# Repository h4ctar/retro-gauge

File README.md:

# Retro Gauge

## Introduction

This is an open source motorcycle tacho project with the following features:

- Analog tachometer
- Digital speedometer
- Odometer
- Trip meter
- Battery voltage
- Standard indicators (turn signals, oil pressure, neutral and high beam)
- Clock

It is housed in a classic round casing, with a retro looking 8 digit starburst LCD.

The toolchain is all open source; the PCB's are designed with KiCad and the case is designed in FreeCAD.

## System Design

The system design is simple, the only interesting decision is that the indicators all go via the microcontroller, this lets us do fun things with the indicators (test them when powered on or reuse the oil pressure indicator for other warnings).

## Microcontroller

An ATmega328P-PU microcontroller will be used to process all the inputs, and drive the outputs.

Here are all the required inputs and outputs:

| Function        | Type           | Number of pins    |
| --------------- | -------------- | ----------------- |
| Tacho           | Digital input  | 1                 |
| Speedo          | Digital input  | 1                 |
| Oil pressure    | Digital input  | 1                 |
| Turn signals    | Digital input  | 1                 |
| Neutral         | Digital input  | 1                 |
| High beam       | Digital input  | 1                 |
| Mode button     | Digital input  | 1                 |
| Battery voltage | Analog input   | 1                 |
| Stepper motor   | Digital output | 4 (could be 3)    |
| RBG LEDs        | Digital output | 1                 |
| LCD             | Digital output | 3                 |
| ISP             | Digital IO     | 3 (can be shared) |
| Real time clock | Digital IO     | 2                 |

For a total of 18 digital IOs and one analog input, the ATmega328P-PU has more than enough at 23 programmable IO lines.

The ATmega328P-PU also has 1024 bytes of EEPROM which can be used to store the configuration, trip and odometer values.

An external 16 MHz crystal will be used to run the ATmega328P-PU at it's fastest clock speed.

The microcontroller will be programmed with an in-circuit serial programmer (ICSP).
A bootloader doesnt need to be burned when using ICSP.

The low byte fuses configure the clock:

| Bit | Name   | Description                                | Value |
| --- | ------ | ------------------------------------------ | ----- |
| 7   | CKDIV8 | When set, divides the clock speed by 8     | 1     |
| 6   | CKOUT  | When set, the clock pulse is output on PB0 | 1     |
| 5   | SUT1   | Sets start up delay time                   | 1     |
| 4   | SUT0   |                                            | 1     |
| 3   | CKSEL3 | Sets the clock source                      | 1     |
| 2   | CKSEL2 |                                            | 1     |
| 1   | CKSEL1 |                                            | 1     |
| 0   | CKSEL0 |                                            | 1     |

The high byte fuses:

| Bit | Name     | Description                               | Value |
| --- | -------- | ----------------------------------------- | ----- |
| 7   | RSTDISBL | External reset disable                    | 1     |
| 6   | DWEN     | Debug wire enable                         | 1     |
| 5   | SPIEN    | Enable serial programming                 | 0     |
| 4   | WDTON    | Watchdog timer always on                  | 1     |
| 3   | EESAVE   | Preserve EEPROM memory through chip erase | 0     |
| 2   | EBOOTSZ1 | Sets the bootloder size memory            | 1     |
| 1   | EBOOTSZ0 |                                           | 1     |
| 0   | BOOTRST  | Select the reset vector                   | 0     |

The extended fuses:

| Bit | Name      | Description                       | Value |
| --- | --------- | --------------------------------- | ----- |
| 7   |           | Not used                          | 1     |
| 6   |           |                                   | 1     |
| 5   |           |                                   | 1     |
| 4   |           |                                   | 1     |
| 3   |           |                                   | 1     |
| 2   | BODLEVEL2 | Sets the brown-out detector level | 1     |
| 1   | BODLEVEL1 |                                   | 0     |
| 0   | BODLEVEL0 |                                   | 1     |

There is a simple Makefile that compiles and links the code and has targets to burn the fuses and the code.

## Power Supply

A linear voltage regulator will be used to convert the bikes rough 14V down to a smooth 5V for the rest of the system.
A smoothing capacitor is added on the bikes side to help smooth out the input before it gets to the regulator.

## Indicator Lights

There are indicator lights for low oil pressure, neutral, high beam and turn signals.

The oil pressure and neutral sensors are simple switches to ground.
So these will be directly connected to digital input pins.
I'm not sure if the internal pull ups will be good enough so there will be provision on the PCB for external pull up resistors.
There will be a diode to protect against connecting this pin to 12V on the bike.

The highbeam and turn signals indicators should light up when they see 12V.
We'll use an optocoupler to give some extra protection.
The left and right turn signals need to go through diodes to stop them turning each other on.

```
Diode forward voltage: 0.715V
Photodiode forward voltage: 1.3V
Photodiode forward current: 10mA
R1 = (14V - 0.715V - 1.3V) / 10mA = 1200 ohm ~= 1k ohm
```

```
CTR: 50%
Output current: 50% of 10mA = 5mA
Output voltage: 4V
R2 = (5V - 4V) / 5mA = 200 ohm
```

## Tachometer

There are a few choices for the tachometer pickup, an inductive or capacitive pickup on one of the spark plug wires, or a hall effect sensor on a rotating part of the engine.
The most robust solution is to go with the hall effect sensor, and the most universal location for it is in replacement of the mechanical drive off the camshaft of the original tachometer.

## Speedometer

The speedometer will also be a hall effect pickup, but will be a simpler design with a few magnets on the wheel and an NPN hall effect sensor mounted on an axel spacer.

## Real Time Clock

A PCF8563T RTC module will be used to keep the time for the clock.
It will have a coin cell to keep the clock ticking when the key is off.

## LCD

The VIM-878-DP-FC-S-LV LCD display will be used.
It is a transflective LCD so works well in both bright sunlight and at night with a backlight.
It is an 8 character 14 (plus 2) segment "starburst" display.
It has a total of (14 + 2) \* 8 = 128 segments and uses 4 backplanes.

The HT1621B will be used to drive the LCD.
There are some existing Arduino libraries to interface with it.
It can drive 32 segments by 4 commons which is exactly what is required to drive the selected LCD.

The schematic of the driver to the display follows the application notes in the datasheet and is optimised for the PCB layout.
It is controlled with 3 pins that are also used by the ICSP.

This table has the LCD segments from the datasheet and what memory address they are according to the PCB layout:

| LCD Pin | COM0 | COM1 | COM2 | COM3 | Memory address |
| ------- | ---- | ---- | ---- | ---- | -------------- |
| 1       | 1D   | 1E   | 1F   | CA1  | 31             |
| 2       | 1L   | 1K   | 1J   | 1I   | 30             |
| 3       | 2D   | 2E   | 2F   | CA2  | 29             |
| 4       | 2L   | 2K   | 2J   | 2I   | 27             |
| 5       | 3D   | 3E   | 3F   | CA3  | 28             |
| 6       | 3L   | 3K   | 3J   | 3I   | 26             |
| 7       | 4D   | 4E   | 4F   | CA4  | 25             |
| 8       | 4L   | 4K   | 4J   | 4I   | 24             |
| 9       | 5D   | 5E   | 5F   | CA5  | 23             |
| 10      | 5L   | 5K   | 5J   | 5I   | 22             |
| 11      | 6D   | 6E   | 6F   | CA6  | 21             |
| 12      | 6L   | 6K   | 6J   | 6I   | 20             |
| 13      | 7D   | 7E   | 7F   | CA7  | 19             |
| 14      | 7L   | 7K   | 7J   | 7I   | 18             |
| 15      | 8D   | 8E   | 8F   | CA8  | 17             |
| 16      | 8L   | 8K   | 8J   | 8I   | 16             |
| 17      | COM0 |      |      |      |                |
| 18      |      | COM1 |      |      |                |
| 19      |      |      | COM2 |      |                |
| 20      |      |      |      | COM3 |                |
| 21      | DP8  | 8C   | 8B   | 8A   | 15             |
| 22      | 8M   | 8N   | 8G   | 8H   | 14             |
| 23      | DP7  | 7C   | 7B   | 7A   | 13             |
| 24      | 7M   | 7N   | 7G   | 7H   | 12             |
| 25      | DP6  | 6C   | 6B   | 6A   | 11             |
| 26      | 6M   | 6N   | 6G   | 6H   | 10             |
| 27      | DP5  | 5C   | 5B   | 5A   | 9              |
| 28      | 5M   | 5N   | 5G   | 5H   | 8              |
| 29      | DP4  | 4C   | 4B   | 4A   | 7              |
| 30      | 4M   | 4N   | 4G   | 4H   | 6              |
| 31      | DP3  | 3C   | 3B   | 3A   | 5              |
| 32      | 3M   | 3N   | 3G   | 3H   | 4              |
| 33      | DP2  | 2C   | 2B   | 2A   | 3              |
| 34      | 2M   | 2N   | 2G   | 2H   | 2              |
| 35      | DP1  | 1C   | 1B   | 1A   | 1              |
| 36      | 1M   | 1N   | 1G   | 1H   | 0              |

From this table we can see that each digit is powered by 4 LCD pins that map to 4 memory addresses.
For example digit 1 is LCD pins 35, 1, 2 and 36, which map to memory address' 1, 31, 30 and 0.

The font maps ASCII characters to the segments in order CA,F,E,D,I,J,K,L,A,B,C,DP,H,G,N,M.
The segments are in this order so the nibbles match the memory layout of the driver.

The address mapping maps digits to the 4 memory addresses that the font nibbles should be written to.

| Digit | Address'   |
| ----- | ---------- |
| 1     |  1,31,30, 0|
| 2     |  3,29,27, 2|
| 3     |  5,28,26, 4|
| 4     |  7,25,24, 6|
| 5     |  9,23,22, 8|
| 6     | 11,21,20,10|
| 7     | 13,19,18,12|
| 8     | 15,17,16,14|

This font table and address mapping should be enough to display text on the LCD.

## Stepper motor

The X27.168 stepper motor will be used, it is designed for gauges and can be directly driven from a microcontroller.

People on the internet say that clamping diodes are required, so they will be added.

The X25 datasheet shows the required pattern to step the motor.

## Indicators

## PCB Design

There are three PCBs: the main board, the sensor board and the face board.
The boards are stacked using standoffs and are connected together with 2.54mm stacking header pins.

The main board has the microcontroller, stepper motor, LCD, real time clock and indicators.
The sensor board has the power supply and the signal conditioning.
The face board is the dial face and has transparent icons for the indicators.

## Case Design

The case is 3D printed out of ASA.

## EEPROM

The ODO, trip and configuration will be stored in EEPROM.

EEPROM has like 100,000 writes before it wears out, so in order to be able to store the ODO and trip we will need to be able to rotate to new address'.
To do this we will have a table at the start of the EEPROM that stores the address of each value and if the EEPROM gets corrupt we will find a new place to store it and update the table.

| Address | Size | Description            |
| ------- | ---- | ---------------------- |
| 0       | 8    | ODO Address            |
| 1       | 8    | Trip Address           |
| 2       | 8    | Wheel diameter         |
| 15      | 8    | Next available address |
| 16      | 32   | ODO value              |
| 20      | 32   | Trip value             |

## Firmware

The source code is in the `firmware/src` directory.

There is a makefile with a default target to compile and link the source into a hex file; a `burn` target to burn this hex to the micro and a `fuses` target to write the fuses.
It is configured to use avrdude and a usbtiny programmer to talk to the microcontroller, but it should be possible to modify it to use other methods.
The code is compiled with clang.
There is a compile_flags.txt file that is used to configure a language server so that Vim or Visual Studio Code can give nice completion and code navigation.

On Arch linux I install the following tools and dependencies:

 * llvm
 * clang
 * avrdude
 * avr-libc
 * lib32-glibc

## Datasheets

 * [ATmega328p](https://ww1.microchip.com/downloads/en/DeviceDoc/Atmel-7810-Automotive-Microcontrollers-ATmega328P_Datasheet.pdf)
 * [HT1621B](https://www.holtek.com/documents/10179/116711/HT1621v321.pdf)
 * [WS2812B](https://www.digikey.com.au/en/datasheets/parallaxinc/parallax-inc-28085-ws2812b-rgb-led-datasheet)

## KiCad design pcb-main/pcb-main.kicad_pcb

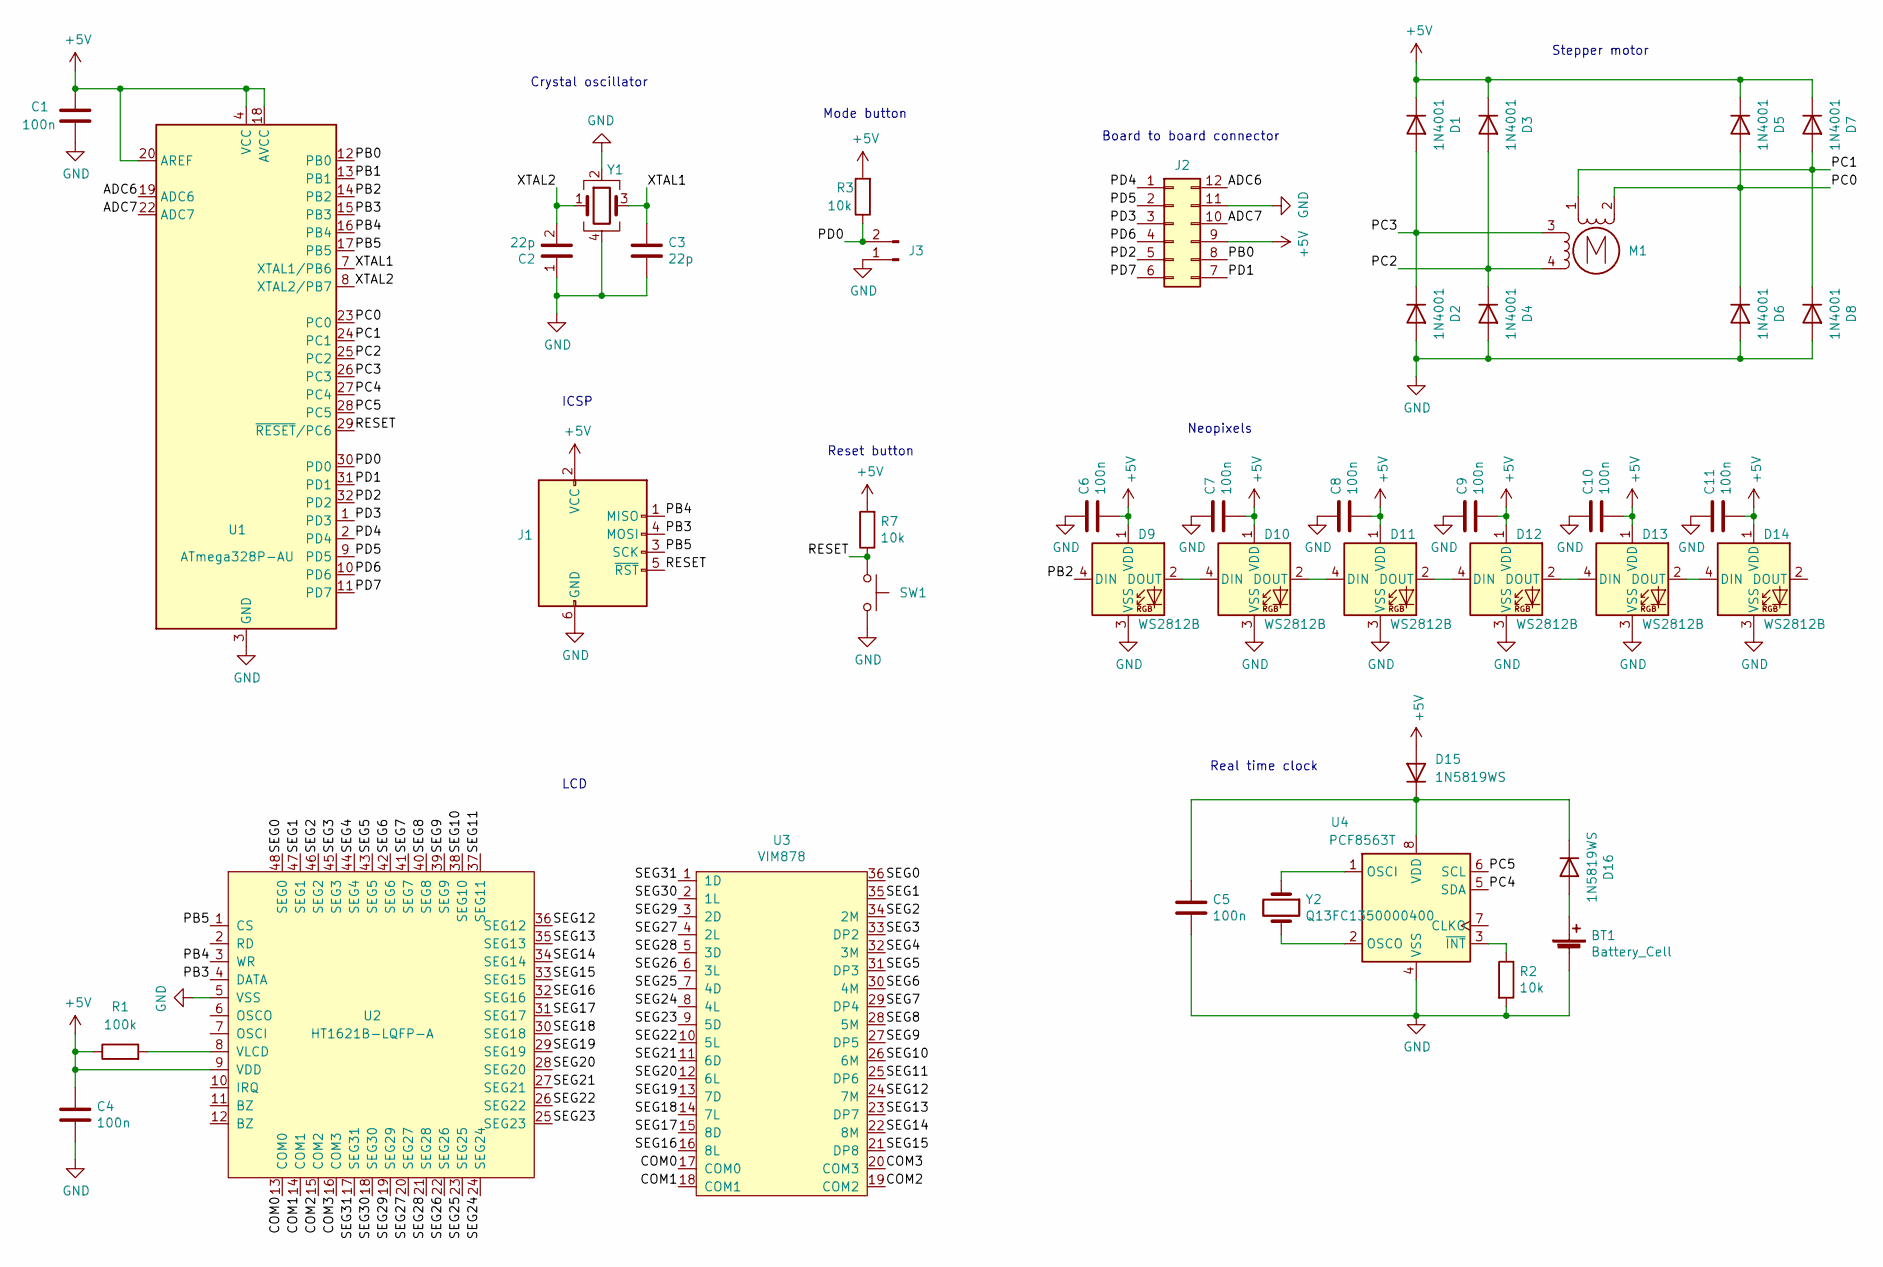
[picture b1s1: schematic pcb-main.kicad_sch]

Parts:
BT1: Battery_Cell; CR1220
C1, C4, C5, C6, C7, C8, C9, C10, C11: 100n; C_0805_2012Metric; LCSC C49678
C2, C3: 22p; C_0805_2012Metric; LCSC C1804
D1, D2, D3, D4, D5, D6, D7, D8: 1N4001; D_1206_3216Metric_Pad1.42x1.75mm_HandSolder
D9, D10, D11, D12, D13, D14: WS2812B; LED_WS2812B_PLCC4_5.0x5.0mm_P3.2mm; LCSC C2761795
D15, D16: 1N5819WS; D_SOD-323; LCSC C191023
J1: AVR-ISP-6; PinHeader_2x03_P2.54mm_Vertical
J2: Conn_02x06_Counter_Clockwise; PinHeader_2x06_P2.00mm_Vertical
J3: Conn_01x02_Male; JST_PH_S2B-PH-K_1x02_P2.00mm_Horizontal
M1: Stepper_Motor; X27.168
R1: 100k; R_0805_2012Metric; LCSC C149504
R2, R3, R7: 10k; R_0805_2012Metric; LCSC C17414
SW1: SW_Push; SW_SPST_TL3342; LCSC C318884
U1: ATmega328P-AU; TQFP-32_7x7mm_P0.8mm; LCSC C14877
U2: HT1621B-LQFP-A; LQFP-48_7x7mm_P0.5mm; LCSC C7532
U3: VIM878
U4: PCF8563T; SOIC-8_3.9x4.9mm_P1.27mm; LCSC C7440
Y1: X322516MLB4SI; Crystal_SMD_3225-4Pin_3.2x2.5mm; LCSC C13738
Y2: Q13FC1350000400; Crystal_SMD_3215-2Pin_3.2x1.5mm; LCSC C32346

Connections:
+5V: C1.1, C4.1, C6.2, C7.2, C8.2, C9.2, C10.2, C11.2, D1.1 (K), D3.1 (K), D5.1 (K), D7.1 (K), D9.1 (VDD), D10.1 (VDD), D11.1 (VDD), D12.1 (VDD), D13.1 (VDD), D14.1 (VDD), D15.2 (A), J1.2 (VCC), J2.9, R1.1, R3.2, R7.2, U1.4 (VCC), U1.6 (VCC), U1.18 (AVCC), U1.20 (AREF), U2.9 (VDD)
/ADC6: J2.12, U1.19 (ADC6)
/ADC7: J2.10, U1.22 (ADC7)
/COM0: U2.13 (COM0), U3.17 (COM0)
/COM1: U2.14 (COM1), U3.18 (COM1)
/COM2: U2.15 (COM2), U3.19 (COM2)
/COM3: U2.16 (COM3), U3.20 (COM3)
/PB0: J2.8, U1.12 (PB0)
/PB1: U1.13 (PB1)
/PB2: D9.4 (DIN), U1.14 (PB2)
/PB3: J1.4 (MOSI), U1.15 (PB3), U2.4 (DATA)
/PB4: J1.1 (MISO), U1.16 (PB4), U2.3 (WR)
/PB5: J1.3 (SCK), U1.17 (PB5), U2.1 (CS)
/PC0: D5.2 (A), D6.1 (K), M1.2 (-), U1.23 (PC0)
/PC1: D7.2 (A), D8.1 (K), M1.1, U1.24 (PC1)
/PC2: D3.2 (A), D4.1 (K), M1.4, U1.25 (PC2)
/PC3: D1.2 (A), D2.1 (K), M1.3, U1.26 (PC3)
/PC4: U1.27 (PC4), U4.5 (SDA)
/PC5: U1.28 (PC5), U4.6 (SCL)
/PD0: J3.2, R3.1, U1.30 (PD0)
/PD1: J2.7, U1.31 (PD1)
/PD2: J2.5, U1.32 (PD2)
/PD3: J2.3, U1.1 (PD3)
/PD4: J2.1, U1.2 (PD4)
/PD5: J2.2, U1.9 (PD5)
/PD6: J2.4, U1.10 (PD6)
/PD7: J2.6, U1.11 (PD7)
/RESET: J1.5 (~RST), R7.1, SW1.1, U1.29 (~RESET/PC6)
/SEG0: U2.48 (SEG0), U3.36
/SEG1: U2.47 (SEG1), U3.35
/SEG2: U2.46 (SEG2), U3.34 (2M)
/SEG3: U2.45 (SEG3), U3.33 (DP2)
/SEG4: U2.44 (SEG4), U3.32 (3M)
/SEG5: U2.43 (SEG5), U3.31 (DP3)
/SEG6: U2.42 (SEG6), U3.30 (4M)
/SEG7: U2.41 (SEG7), U3.29 (DP4)
/SEG8: U2.40 (SEG8), U3.28 (5M)
/SEG9: U2.39 (SEG9), U3.27 (DP5)
/SEG10: U2.38 (SEG10), U3.26 (6M)
/SEG11: U2.37 (SEG11), U3.25 (DP6)
/SEG12: U2.36 (SEG12), U3.24 (7M)
/SEG13: U2.35 (SEG13), U3.23 (DP7)
/SEG14: U2.34 (SEG14), U3.22 (8M)
/SEG15: U2.33 (SEG15), U3.21 (DP8)
/SEG16: U2.32 (SEG16), U3.16 (8L)
/SEG17: U2.31 (SEG17), U3.15 (8D)
/SEG18: U2.30 (SEG18), U3.14 (7L)
/SEG19: U2.29 (SEG19), U3.13 (7D)
/SEG20: U2.28 (SEG20), U3.12 (6L)
/SEG21: U2.27 (SEG21), U3.11 (6D)
/SEG22: U2.26 (SEG22), U3.10 (5L)
/SEG23: U2.25 (SEG23), U3.9 (5D)
/SEG24: U2.24 (SEG24), U3.8 (4L)
/SEG25: U2.23 (SEG25), U3.7 (4D)
/SEG26: U2.22 (SEG26), U3.6 (3L)
/SEG27: U2.20 (SEG27), U3.4 (2L)
/SEG28: U2.21 (SEG28), U3.5 (3D)
/SEG29: U2.19 (SEG29), U3.3 (2D)
/SEG30: U2.18 (SEG30), U3.2 (1L)
/SEG31: U2.17 (SEG31), U3.1 (1D)
/XTAL1: C3.1, U1.7 (XTAL1/PB6), Y1.3
/XTAL2: C2.2, U1.8 (XTAL2/PB7), Y1.1
GND: BT1.2 (-), C1.2, C2.1, C3.2, C4.2, C5.2, C6.1, C7.1, C8.1, C9.1, C10.1, C11.1, D2.2 (A), D4.2 (A), D6.2 (A), D8.2 (A), D9.3 (VSS), D10.3 (VSS), D11.3 (VSS), D12.3 (VSS), D13.3 (VSS), D14.3 (VSS), J1.6 (GND), J2.11, J3.1, R2.2, SW1.2, U1.3 (GND), U1.5 (GND), U1.21 (GND), U2.5 (VSS), U4.4 (VSS), Y1.2, Y1.4
unnamed: BT1.1 (+), D16.2 (A)
unnamed: C5.1, D15.1 (K), D16.1 (K), U4.8 (VDD)
unnamed: D10.2 (DOUT), D11.4 (DIN)
unnamed: D9.2 (DOUT), D10.4 (DIN)
unnamed: D11.2 (DOUT), D12.4 (DIN)
unnamed: D12.2 (DOUT), D13.4 (DIN)
unnamed: D13.2 (DOUT), D14.4 (DIN)
unnamed: R1.2, U2.8 (VLCD)
unnamed: R2.1, U4.3 (~INT)
unnamed: U4.1 (OSCI), Y2.1
unnamed: U4.2 (OSCO), Y2.2

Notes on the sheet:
Stepper motor
Reset button
Neopixels
ICSP
Mode button
Real time clock
Board to board connector
LCD
Crystal oscillator

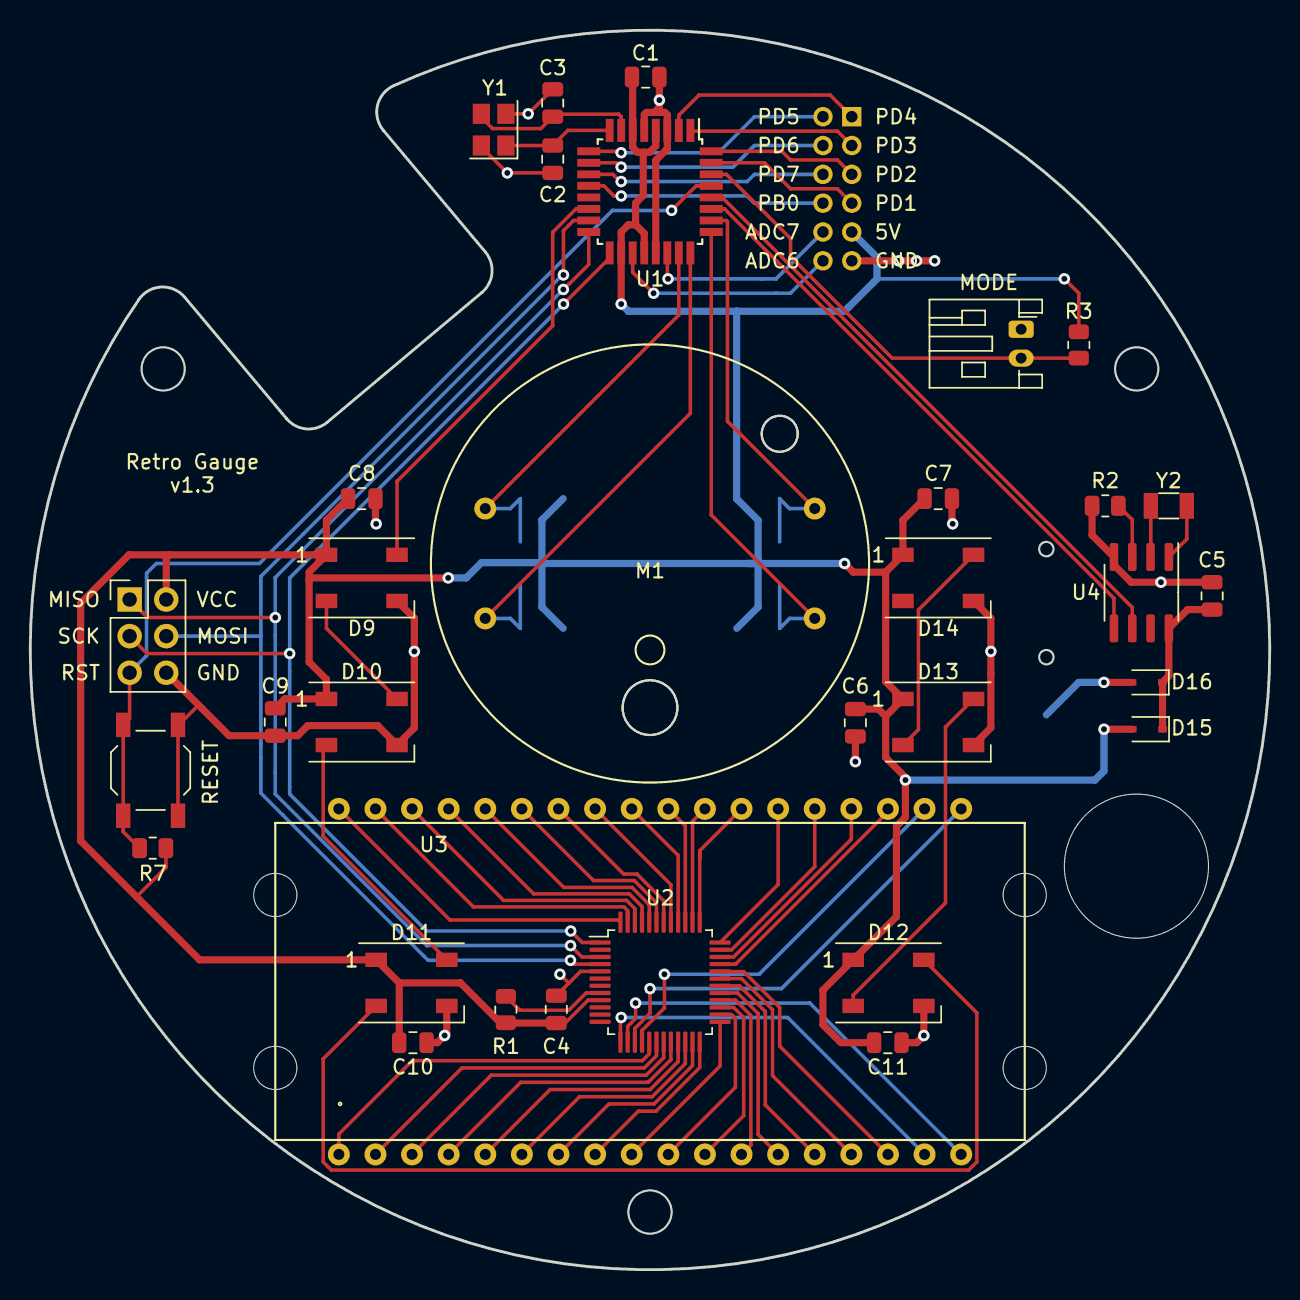
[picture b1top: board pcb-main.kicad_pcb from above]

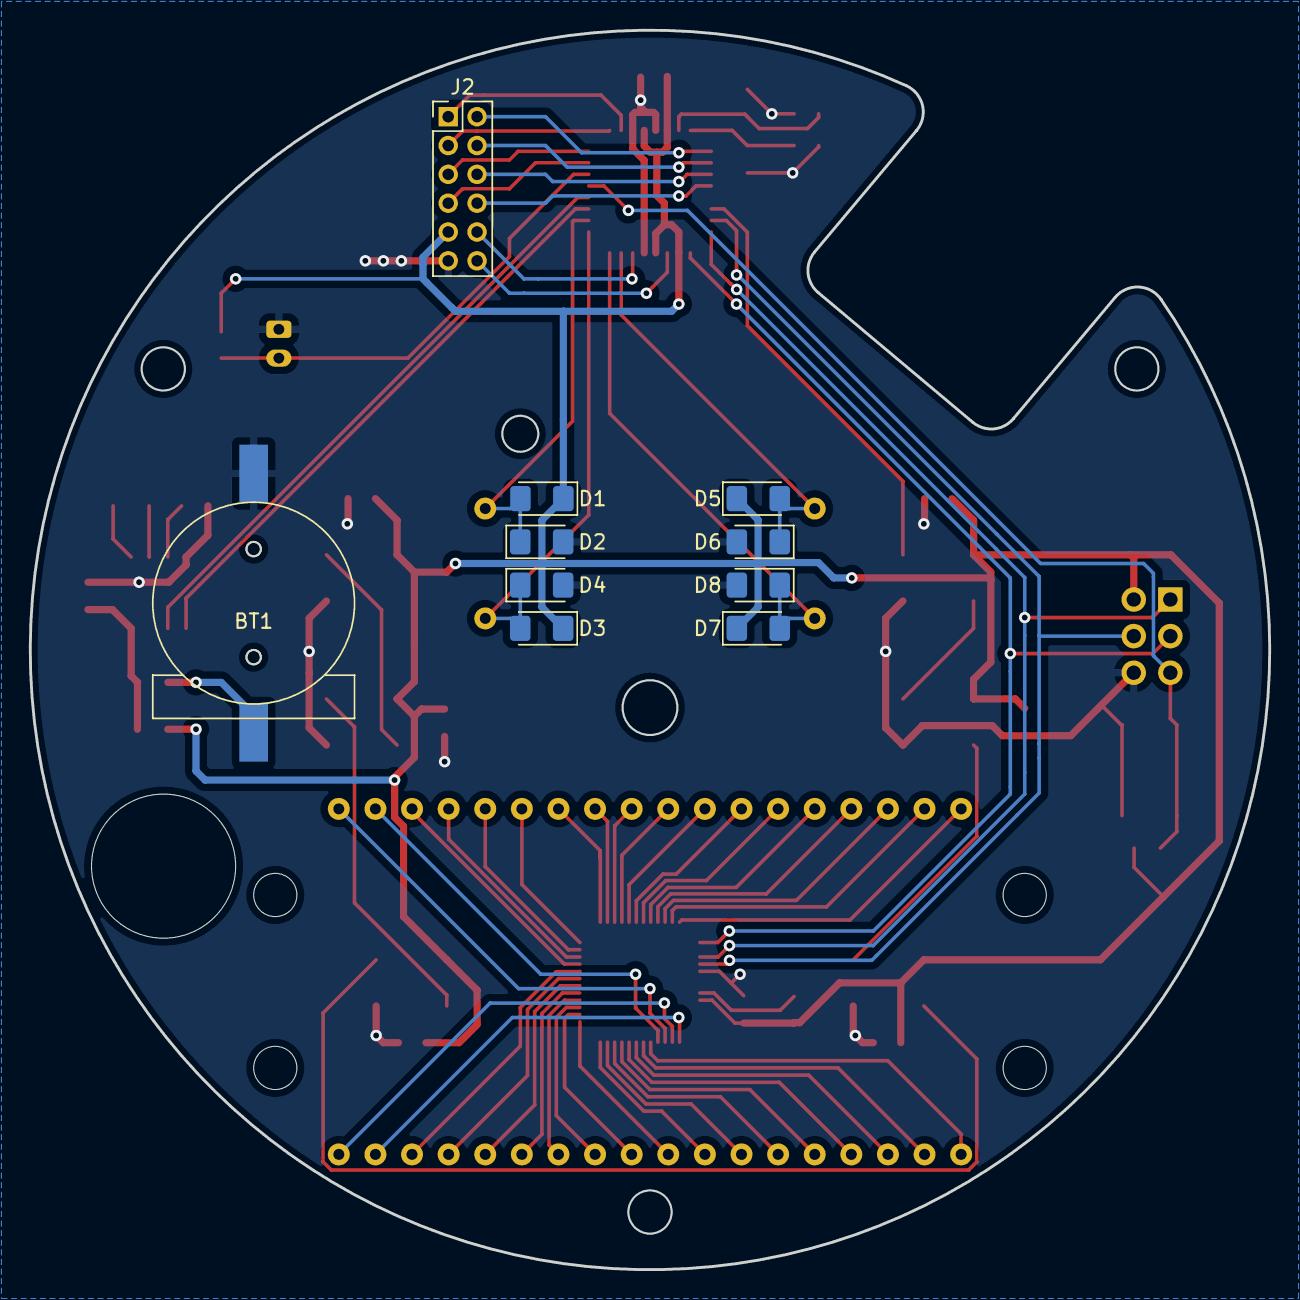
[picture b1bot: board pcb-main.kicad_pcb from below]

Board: 2 copper layers, 86.0 x 86.0 mm, 43 parts (10 on the bottom side), 73 nets.

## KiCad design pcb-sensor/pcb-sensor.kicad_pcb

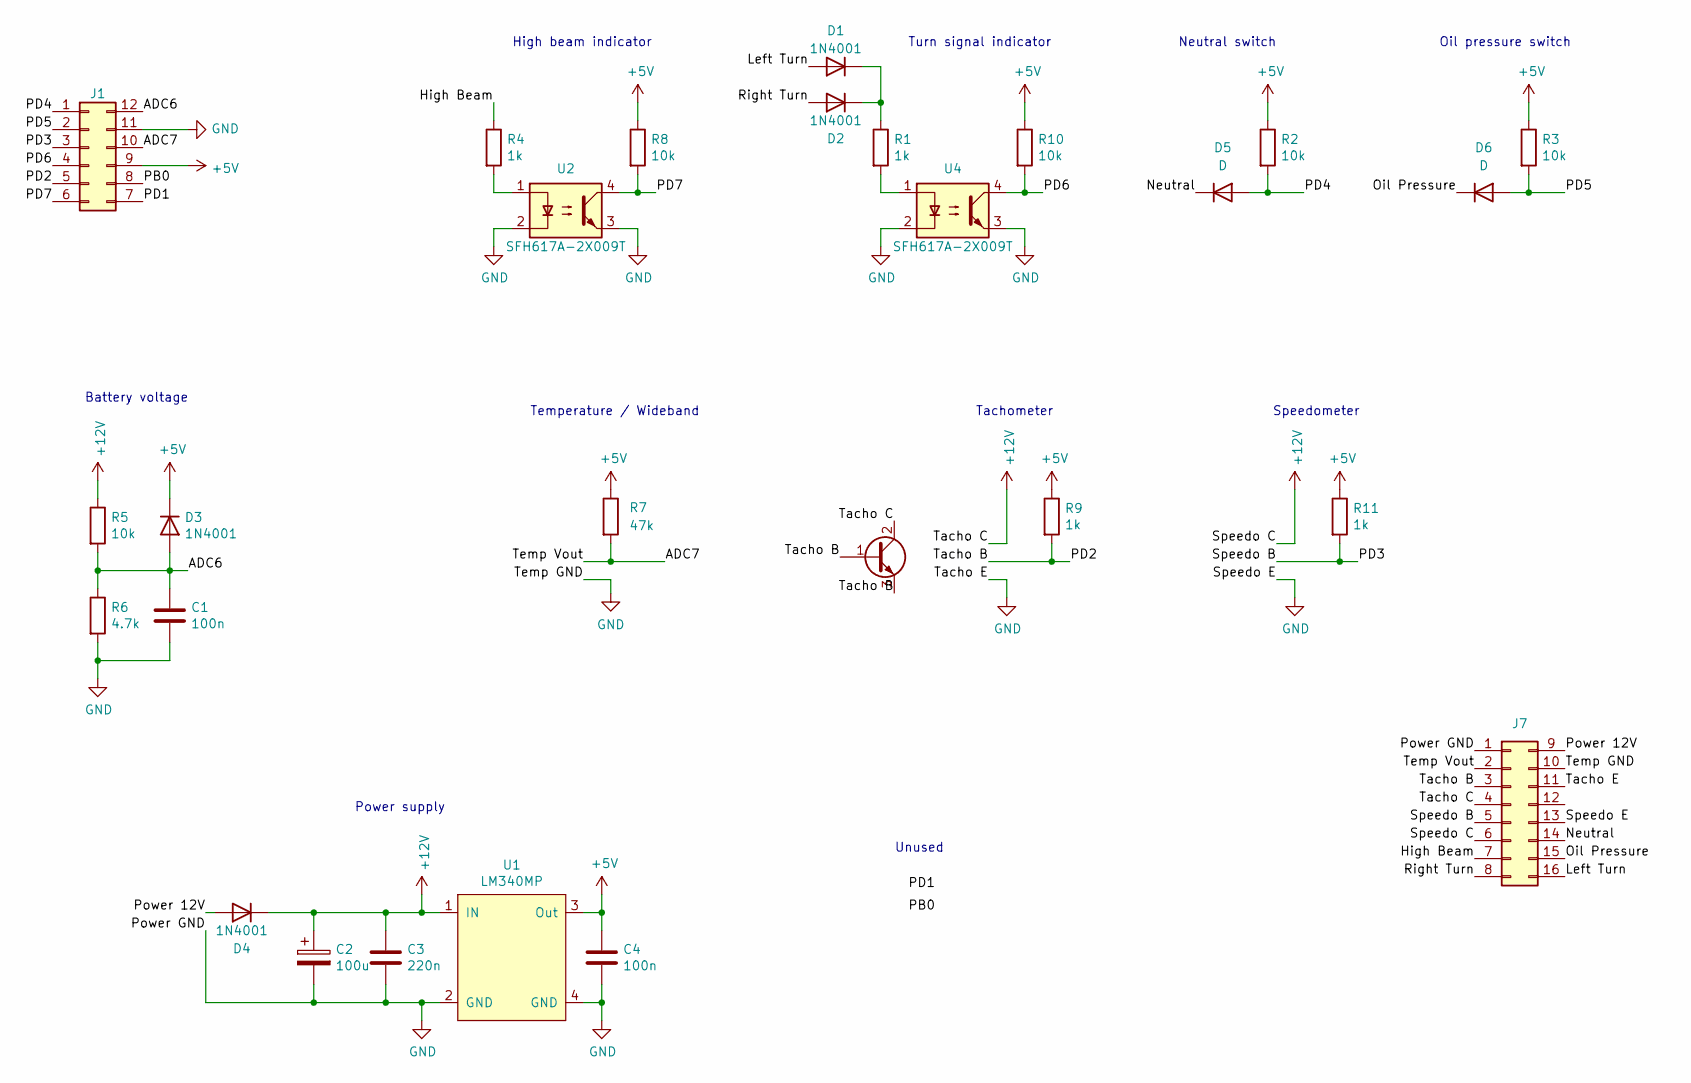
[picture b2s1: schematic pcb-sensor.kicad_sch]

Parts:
C1, C4: 100n; C_1206_3216Metric_Pad1.33x1.80mm_HandSolder
C2: 100u; CP_Radial_D8.0mm_P3.80mm
C3: 220n; C_1206_3216Metric_Pad1.33x1.80mm_HandSolder
D1, D2, D3, D4: 1N4001; D_1206_3216Metric_Pad1.42x1.75mm_HandSolder
D5, D6: D; D_1206_3216Metric_Pad1.42x1.75mm_HandSolder
J1: Conn_02x06_Counter_Clockwise; PinSocket_2x06_P2.00mm_Vertical
J7: Conn_02x08_Top_Bottom; Molex_Mini-Fit_Jr_5566-16A_2x08_P4.20mm_Vertical
R1, R4, R9, R11: 1k; R_1206_3216Metric_Pad1.30x1.75mm_HandSolder
R2, R3, R5, R8, R10: 10k; R_1206_3216Metric_Pad1.30x1.75mm_HandSolder
R6: 4.7k; R_1206_3216Metric_Pad1.30x1.75mm_HandSolder
R7: 47k; R_1206_3216Metric_Pad1.30x1.75mm_HandSolder
U1: LM340MP; SOT-223
U2, U4: SFH617A-2X009T; SMDIP-4_W7.62mm

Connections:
+5V: C4.1, D3.1 (K), J1.9, R2.1, R3.1, R7.1, R8.1, R9.1, R10.1, R11.1, U1.3 (Out)
+12V: C2.1, C3.1, D4.1 (K), J7.4, J7.6, R5.1, U1.1 (IN)
/ADC6: C1.1, D3.2 (A), J1.12, R5.2, R6.1
/High Beam: J7.7, R4.1
/Left Turn: D1.2 (A), J7.16
/Neutral: D5.1 (K), J7.14
/Oil Pressure: D6.1 (K), J7.15
/PB0: J1.8
/PD1: J1.7
/PD4: D5.2 (A), J1.1, R2.2
/PD5: D6.2 (A), J1.2, R3.2
/PD6: J1.4, R10.2, U4.4
/PD7: J1.6, R8.2, U2.4
/Power 12V: D4.2 (A), J7.9
/Right Turn: D2.2 (A), J7.8
/Speedo B: J1.3, J7.5, R11.2
/Tacho B: J1.5, J7.3, R9.2
/Temp Vout: J1.10, J7.2, R7.2
GND: C1.2, C2.2, C3.2, C4.2, J1.11, J7.1, J7.10, J7.11, J7.13, R6.2, U1.2 (GND), U1.4 (GND), U2.2, U2.3, U4.2, U4.3
unnamed: D1.1 (K), D2.1 (K), R1.1
unnamed: R1.2, U4.1
unnamed: R4.2, U2.1

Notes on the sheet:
Tachometer
Neutral switch
Unused
High beam indicator
Power supply
Battery voltage
Temperature / Wideband
Turn signal indicator
Oil pressure switch
Speedometer

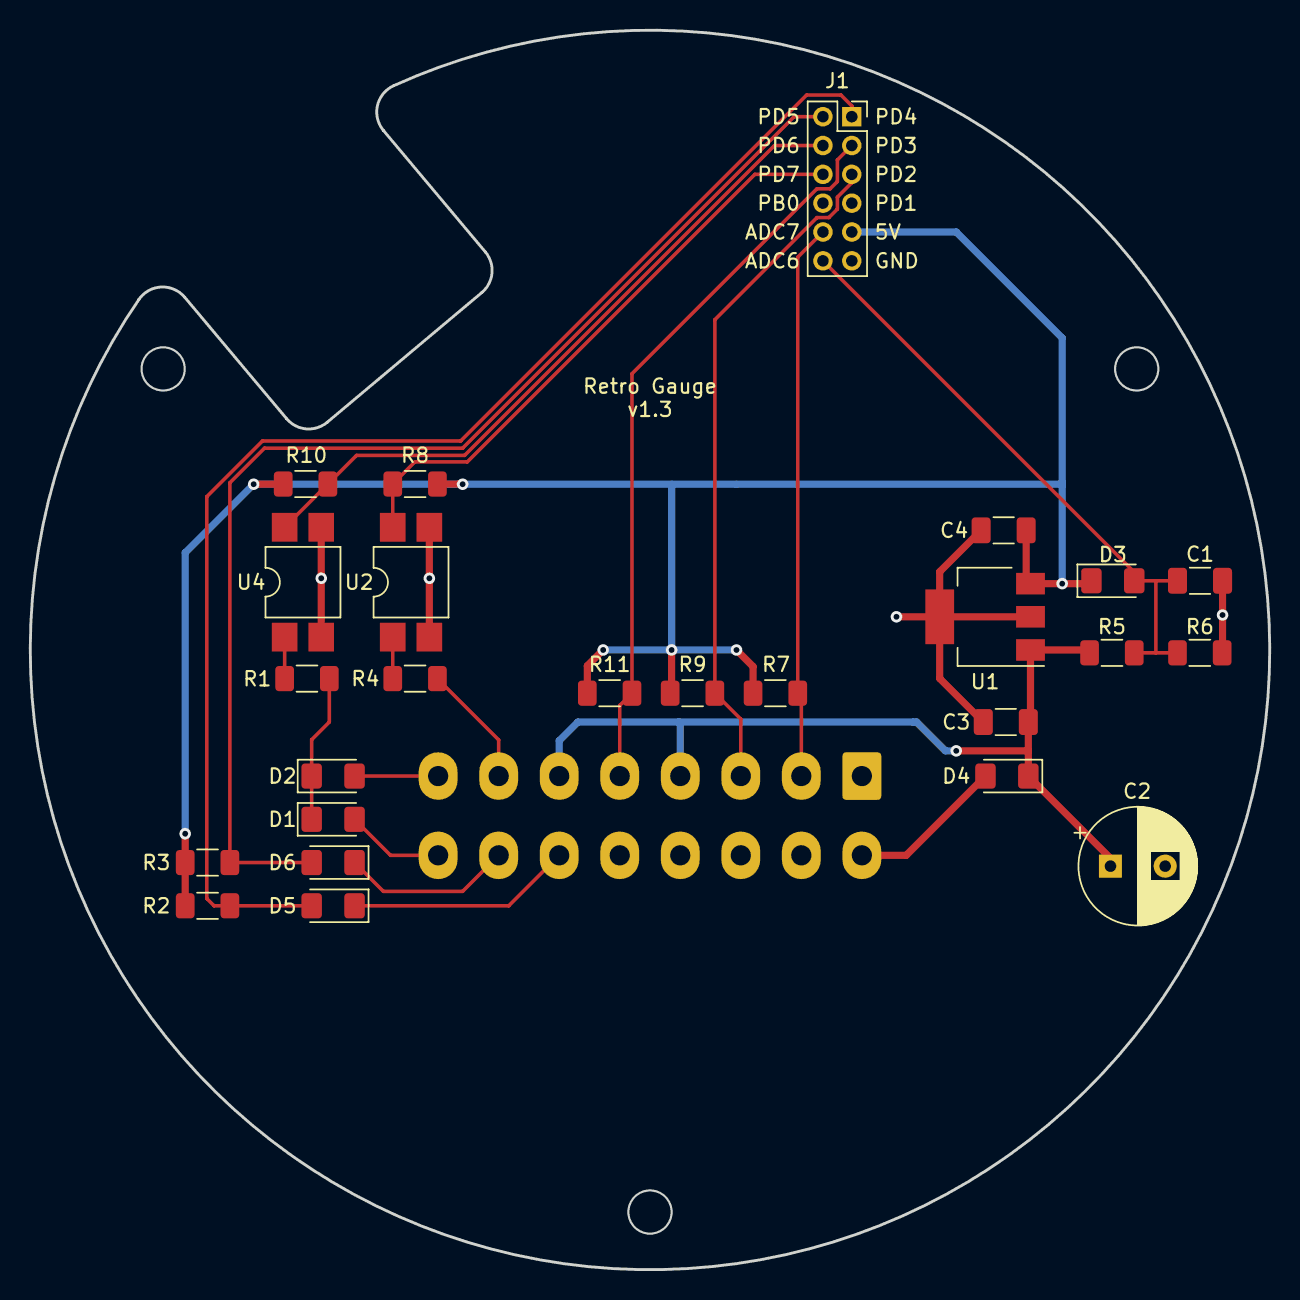
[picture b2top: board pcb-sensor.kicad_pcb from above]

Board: 2 copper layers, 86.0 x 86.0 mm, 26 parts (1 on the bottom side), 20 nets.

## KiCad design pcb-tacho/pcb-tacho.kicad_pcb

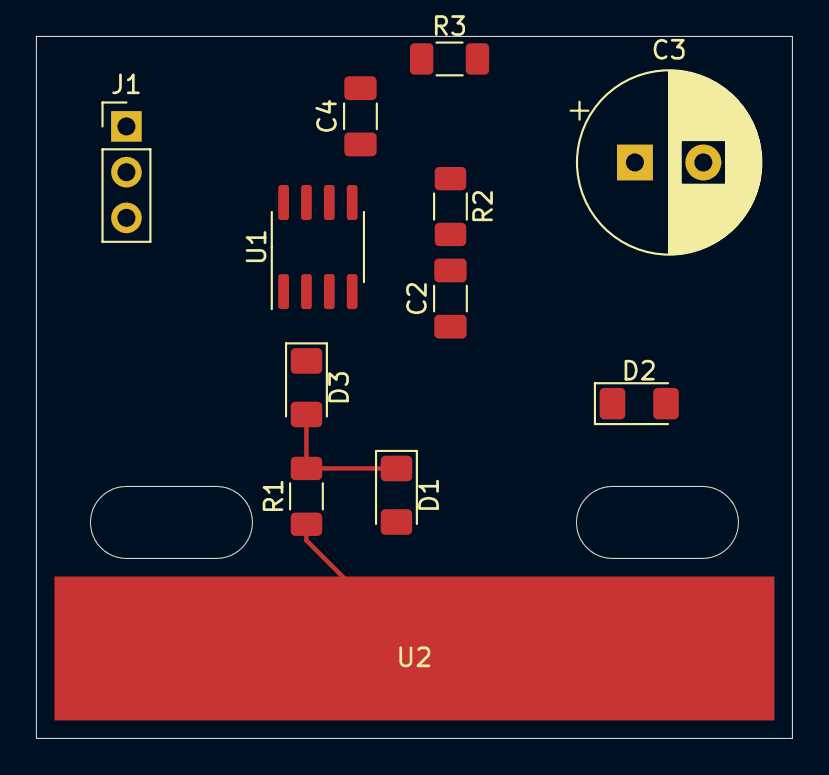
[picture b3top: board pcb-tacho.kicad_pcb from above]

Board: 2 copper layers, 42.0 x 39.0 mm, 12 parts (0 on the bottom side), 8 nets.

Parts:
C2: 100p; C_1206_3216Metric_Pad1.33x1.80mm_HandSolder
C3: 10u; CP_Radial_D10.0mm_P3.80mm
C4: 10n; C_1206_3216Metric_Pad1.33x1.80mm_HandSolder
D1: 5V; D_1206_3216Metric_Pad1.42x1.75mm_HandSolder
D2: 9V; D_1206_3216Metric_Pad1.42x1.75mm_HandSolder
D3: D; D_1206_3216Metric_Pad1.42x1.75mm_HandSolder
J1: Conn_01x03_Male; PinHeader_1x03_P2.54mm_Vertical
R1: 1k; R_1206_3216Metric_Pad1.30x1.75mm_HandSolder
R2: 47k; R_1206_3216Metric_Pad1.30x1.75mm_HandSolder
R3: 15; R_1206_3216Metric_Pad1.30x1.75mm_HandSolder
U1: LM555xM; SOIC-8_3.9x4.9mm_P1.27mm
U2: TachoCapPlate

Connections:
+9V: C3.1, D2.1, R2.1, R3.2, U1.4, U1.8
+12V: J1.1, R3.1
GND: C2.1, C3.2, C4.2, D1.2, D2.2, J1.3, U1.1
unnamed: C2.2, R2.2, U1.6, U1.7
unnamed: C4.1, U1.5
unnamed: D1.1, D3.2, R1.2
unnamed: D3.1, U1.2
unnamed: J1.2, U1.3

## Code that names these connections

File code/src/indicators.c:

#include "indicators.h"

#include <avr/io.h>

#include "led.h"

#define INDICATOR_PIN       PIND
#define INDICATOR_DDR       DDRD
#define OIL_MASK            (1 << PD3)
#define TURN_SIGNAL_MASK    (1 << PD5)
#define HIGH_BEAM_MASK      (1 << PD4)
#define NEUTRAL_MASK        (1 << PD6)

void initIndicators() {
    // Make the indicator pins inputs
    INDICATOR_DDR &= ~(OIL_MASK | TURN_SIGNAL_MASK | HIGH_BEAM_MASK | NEUTRAL_MASK);

    // Turn on all the LEDS
    long ledColors[] = {YELLOW, BLUE, WHITE, WHITE, GREEN, RED};
    writeLeds(ledColors, 6);
}

void updateIndicators() {
    long oilLedColor = INDICATOR_PIN & OIL_MASK ? OFF : RED;
    long turnSignalLedColor = OFF; // INDICATOR_PIN & TURN_SIGNAL_MASK ? OFF : YELLOW;
    long highBeamLedColor = OFF; // INDICATOR_PIN & HIGH_BEAM_MASK ? OFF : BLUE;
    long neutralLedColor = INDICATOR_PIN & NEUTRAL_MASK ? OFF : GREEN;
    long ledColors[] = {turnSignalLedColor, highBeamLedColor, OFF, OFF, neutralLedColor, oilLedColor};
    writeLeds(ledColors, 6);
}

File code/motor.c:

#include <avr/io.h>
#include <stdint.h>

#include "motor.h"
#include "timer.h"

#define MOT_PORT    PORTC
#define MOT_DDR     DDRC
#define MOT_1_MASK  (1 << PC1)
#define MOT_2_MASK  (1 << PC0)
#define MOT_3_MASK  (1 << PC3)
#define MOT_4_MASK  (1 << PC2)

#define MOT_PATTERN_4 0b00000111
#define MOT_PATTERN_3 0b00011100
#define MOT_PATTERN_2 0b00011100
#define MOT_PATTERN_1 0b00110001

#define STEP_PERIOD 1000

#define min(a,b) \
   ({ __typeof__ (a) _a = (a); \
       __typeof__ (b) _b = (b); \
     _a < _b ? _a : _b; })

#define max(a,b) \
   ({ __typeof__ (a) _a = (a); \
       __typeof__ (b) _b = (b); \
     _a > _b ? _a : _b; })

uint32_t lastStepTime = 0;
uint16_t currentSteps = 0;
uint16_t targetSteps = 0;

void waitForMotor();
void stepMotor();

void initMotor() {
    MOT_DDR |= MOT_1_MASK;
    MOT_DDR |= MOT_2_MASK;
    MOT_DDR |= MOT_3_MASK;
    MOT_DDR |= MOT_4_MASK;

    // Home the motor
    setMotorTargetPosition(12);
    waitForMotor();
    setMotorTargetPosition(0);
    waitForMotor();
}

void setMotorTargetPosition(float position) {
    targetSteps = max(min(position * 60, 12 * 60), 0);
}

float getMotorCurrentPosition() {
    return currentSteps / 60.f;
}

void updateMotor() {
    uint32_t currentTime = micros();
    if (currentTime - lastStepTime >= STEP_PERIOD) {
        int16_t delta = targetSteps - currentSteps;
        int8_t direction = (delta > 0) - (delta < 0);

        currentSteps += direction;

        stepMotor();

        lastStepTime = currentTime;
    }
}

void waitForMotor() {
    while (currentSteps != targetSteps) {
        updateMotor();
    }
}

void stepMotor() {
    uint8_t step = currentSteps % 6;

    if ((MOT_PATTERN_1 >> step) & 1)
        MOT_PORT |= MOT_1_MASK;
    else
        MOT_PORT &= ~MOT_1_MASK;

    if ((MOT_PATTERN_2 >> step) & 1)
        MOT_PORT |= MOT_2_MASK;
    else
        MOT_PORT &= ~MOT_2_MASK;

    if ((MOT_PATTERN_3 >> step) & 1)
        MOT_PORT |= MOT_3_MASK;
    else
        MOT_PORT &= ~MOT_3_MASK;

    if ((MOT_PATTERN_4 >> step) & 1)
        MOT_PORT |= MOT_4_MASK;
    else
        MOT_PORT &= ~MOT_4_MASK;
}

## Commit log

2021-09-04 updated circuit for spike
2021-09-10 lcd and mcu
2021-09-18 added stepper motor spike (and heaps of other stuff)
2021-09-18 cleaned up main pcb
2021-09-19 sensor pcb
2021-09-26 v1.0
2021-10-10 initial case 3d model
2021-10-16 add tacho sensor circuit
2021-10-16 updated case 3d model
2021-10-16 added photos of spikes
2021-10-16 add oshw logo
2021-11-09 made pcb bigger
2021-11-09 reset button label
2021-11-27 started v1.1
2021-11-27 more v1.1
2021-12-02 panelize
2021-12-03 makefile
2021-12-12 v1.1
2021-12-21 fix delay
2021-12-22 lcd spike
2021-12-29 led and lcd code
2021-12-29 timer
2021-12-29 motor codez
2021-12-29 lcd buffer
2021-12-30 added licence
2021-12-30 migrate to kicad 6
2021-12-30 battery voltage
2022-01-29 led shield
2022-01-29 tacho sensor pcb
2022-01-29 fixed broken link
2022-01-29 code cleanup
2022-01-29 removed spikes
2022-01-29 removed vscode
2022-02-05 mode button
2022-02-05 mode title display
2022-02-05 clean up
2022-02-05 smoothing
2022-02-05 smoothing for speedo
2022-02-05 display units
2022-02-05 added clock
2022-02-06 odo and trip
2022-02-06 clean up'
2022-03-05 simplified the speedo code
2022-03-06 resolves #32: warning indicator symbol
2022-03-06 resolves #29: move needle pin
2022-03-06 resolves #22: see through indicator icons
2022-03-06 resolves #27: move rtc capacitor closer to ic
2022-03-06 resolves #30: odo in eeprom
2022-03-06 resolves #35: 32bit odo
2022-03-06 resolves #36: better long press
2022-03-06 resolves #34: eeprom rotation
2022-03-06 resolves #21: reset button
2022-03-06 fix table layout in readme
2022-03-08 resolves #31: set clock time
2022-03-11 resolves #37: optocoupler footprint
2022-03-13 model cleanup
2022-03-13 3d model assembly
2022-08-27 make improvements
2022-09-10 resolves #43: reduce hall effect sensor pull up to remove noise
2022-09-11 removed unused files
2022-09-11 updated compile flags
2022-09-11 resolves #42: fix clock set wrap
2022-09-11 remove kicad 4 files
2022-09-11 rename code to firmware
2022-09-11 resolves #13: lcd brightness pot
2022-09-17 resolves #40: fix 3d models
2022-09-17 resolves #39: smd crystals
2022-09-17 resolves #18: integrated mode button
2022-09-17 resolves #26: protection diodes
2022-09-17 resolves #17: interrupt pin
2022-09-17 changed pot
2022-09-17 resolves #47: update silkscreen labels
2022-09-17 updated turnsignal requirement from 2 to 1 input
2022-09-17 resolves #46: mode button connector
2022-10-01 openscad
2022-10-01 led indicator cleanup
2022-10-01 document firmware
2022-10-09 deleted tacho
2022-10-09 changed lcd resistor to 100k
2022-10-14 resolves #52: crystal circuit
2022-10-14 speedo INT0
2022-10-14 neopixel only when change
2022-10-15 resolves #48: neopixel caps
2022-10-15 pcb cleanup
2022-10-28 update layout
2022-10-30 update pcb layouts
2022-11-13 v1.3 last minute changes
2023-02-04 updated pins
2023-02-04 updated pcb outline
2023-02-04 new case design
